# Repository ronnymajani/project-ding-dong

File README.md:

# Project Ding Dong
An automated doorbell that messages you via a Telegram channel whenever someone rings your doorbell. Powered by the ESP8266
###### [Full Project Description at Hackaday.io](https://hackaday.io/project/61540-project-ding-dong)
------------------------

***The README is not yet complete***

### NOTE:
I omitted a file called `credentials.py` in which I store the TOKEN of my bot and the channel ID that it will push messages to.
So to be able to get the code running don't forget to create this file in the folder `code` and fill it as follows:
``` python
# credentials.py

# This is the generated access token for your telegram bot
TOKEN = ""
# This is the chat id of the channel your bot will push messages to
CHANNEL_ID = ""
# wireless credentials
WIFI_SSID = ""
WIFI_PASS = ""
```

Tools Used:
-------------
- **OpenSCAD** to edit the 3D models for the chassis
- **Telegram** to be able to communicate with the *doorbell*
- **Eagle** to be able to edit the electronic schematics
- **esptool** for flashing the ESP8266
- **mpfshell** for easily transfering files from the computer to the ESP8266

Repository layout:
----------
- **chassis:** this folder contains the OpenSCAD files for the chassis that encompasses the entire system
- **code:** this folder contains the code that will run on the ESP8266
- **schematics:** this folder contains the electronic schematics files that are used to make the PCB board

Third Party Resources and Useful Links:
----------------------
- [Micropython for the ESP8266 Read the Docs page](https://docs.micropython.org/en/latest/esp8266/index.html)
- [urequests.py micropython module](https://github.com/micropython/micropython-lib/blob/master/urequests/urequests.py)
- [Telegram Bots API](https://core.telegram.org/bots/api)
- [mpfshell github page](https://github.com/wendlers/mpfshell)
- [Nice article explaining how to hook up a LiPo battery to the ESP8266](https://randomnerdtutorials.com/esp8266-voltage-regulator-lipo-and-li-ion-batteries/)
- [EagleCAD Library for most/all ESP8266 variants](https://github.com/wvanvlaenderen/ESP8266-Eagle_Library)
- [OpenSCAD Socket Design for the ESP8266-07](https://github.com/makertum/ESP8266-RNS)
- [How to get the your telegram channel's id](https://github.com/GabrielRF/telegram-id#web-channel-id)
- [Eagle CAD library for Microchip components](https://www.element14.com/community/docs/DOC-64255/l/microchip-cad-library-for-cadsoft-eagle-software)
- [Eagle CAD library for basic parts by itead.cc (*like the BC557 PNP BJT*)](https://www.itead.cc/blog/eagle-library-for-basic-parts-series)

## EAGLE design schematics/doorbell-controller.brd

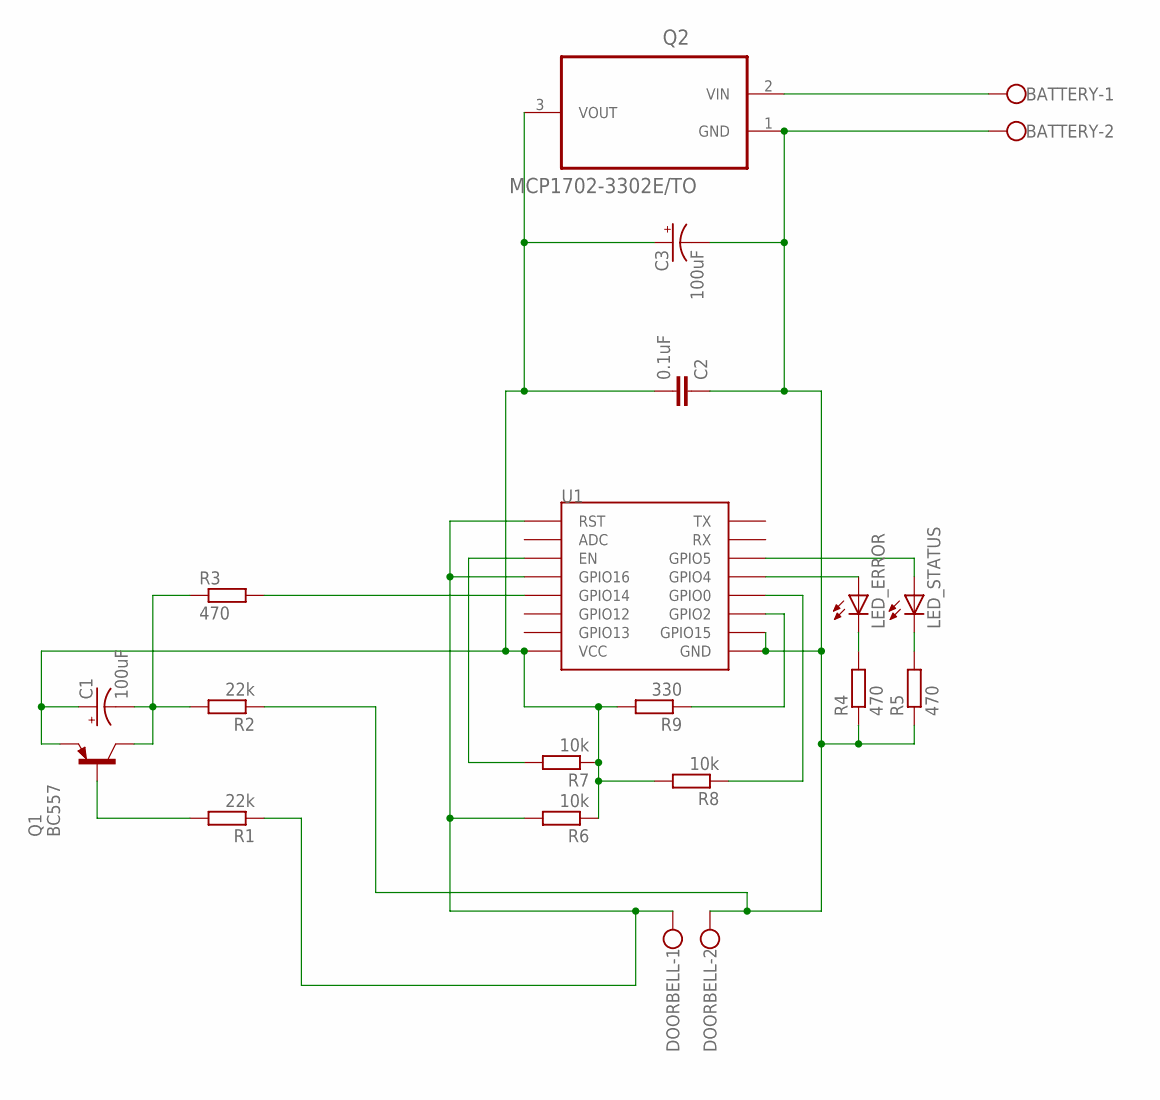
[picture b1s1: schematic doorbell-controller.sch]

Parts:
BATTERY: W237-102
C1, C3: 100uF; E2,5-6E
C2: 0.1uF; C025-025X050
DOORBELL: W237-102
LED_ERROR: LED5MM
LED_STATUS: LED5MM
Q1: BC557; TO92
Q2: MCP1702-3302E/TO; TO127P254X533-3
R1, R2: 22k; 0204/7
R3, R4, R5: 470; 0204/7
R6, R7, R8: 10k; 0204/7
R9: 330; 0204/7
U1: ESP12-TR

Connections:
BATT_VIN: BATTERY.1, Q2.2 (VIN)
GND: BATTERY.2, C2.1, C3.-, DOORBELL.2, Q2.1 (GND), R2.1, R4.1, R5.1, U1.GND, U1.GPIO15
unnamed: LED_STATUS.A, U1.GPIO5
unnamed: Q1.2 (B), R1.2
unnamed: R3.2, U1.GPIO14
unnamed: LED_ERROR.A, U1.GPIO4
unnamed: C1.-, Q1.3 (C), R2.2, R3.1
unnamed: LED_ERROR.K (C), R4.2
unnamed: LED_STATUS.K (C), R5.2
unnamed: R9.1, U1.GPIO2
unnamed: R7.2, U1.EN
unnamed: R8.1, U1.GPIO0
RST: DOORBELL.1, R1.1, R6.2, U1.GPIO16, U1.RST
VCC: C1.+, C2.2, C3.+, Q1.1 (E), Q2.3 (VOUT), R6.1, R7.1, R8.2, R9.2, U1.VCC

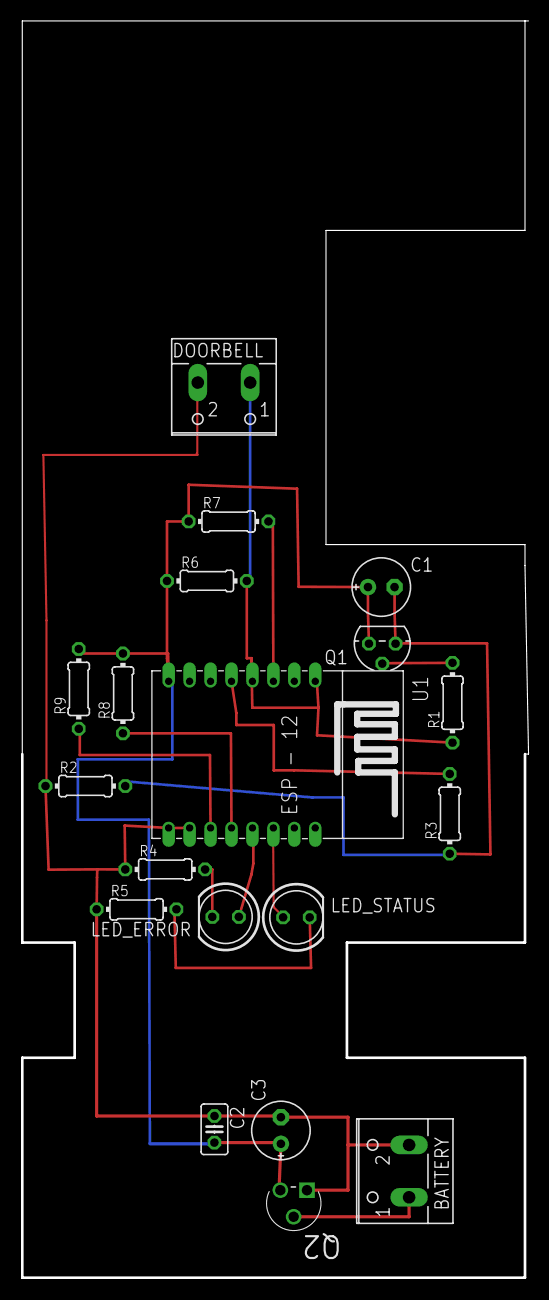
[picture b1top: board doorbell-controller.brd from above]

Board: 2 copper layers, 48.2 x 119.9 mm, 19 parts (0 on the bottom side), 14 nets.

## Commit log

2018-02-22 Initial Commit; Testing Telegram Bot API
2018-02-22 Began OpenSCAD design of chassis
2018-02-22 Moved Source code into separate folder
2018-02-22 Extracted Globals to separate file
2018-02-22 Created a Scene file; Made chassis modular
2018-02-22 Added ESP8266 Mount (found it on github)
2018-02-22 Created Eagle Project for schematics; Modified ESP8266 Library
    I had to modify the ESP8266 library, because I have a modified ESP-12 chip that has the GPIO5 and GPIO4 pins swaped
2018-02-22 Renamed folder to 'schematics'
2018-02-22 Created Schematics file; Updated Readme
2018-02-22 Created pass.py to store bot token and channel_id
2018-02-22 Added pass.py to .gitignore
2018-02-22 Stopped Tracking pass.py
2018-02-22 renamed pass.py to credentials.py
2018-02-23 Added class to deal with Telegram Bot API
2018-02-23 created static class for managing the network interface
2018-02-23 added boot.py file; called NetworkManager's init function
2018-02-23 renamed myapp.py to main.py
2018-02-23 added check for isconnected
2018-02-23 Using latest urequests.py from github repo
2018-02-25 Implemented timeout functionality for connect function
2018-02-25 Added Comments; Used static function calls when possible
2018-02-25 Check if the device woke up due to an interrupt or due to RTC timeout
2018-02-25 Removed infinite loop; Changed message being sent
2018-02-25 Added interrupt extender to schematics
2018-02-25 Added LEDs to schematics; Replaces button with Clamp
2018-02-25 Hooked up RST to GPIO16
2018-02-25 Added disable function; Connect returns True if already connected
2018-02-25 Decreased CPU frequency; Set sleep mode
2018-02-25 Added more constants
2018-02-25 Abstracted the main operations into a helpers.py file
2018-02-25 Uses helpers.py; Uses LEDs; Handles multiple "knocks"
2018-02-25 Removed redundant "knock again" function
    Since the doorbell is hardwired to the RST pin, there's no way to prevent the device from resetting when the doorbell is knocked therefore, it's redundant to make a loop and check for another press o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
2018-02-25 Added check for Telegram send message failure
2018-02-25 Updated Schematics to fit wall mount dimensions
2018-02-25 Added voltage regulator to schematics
2018-02-25 Updated .gitignore
2018-02-25 Exported pdf of schematics
